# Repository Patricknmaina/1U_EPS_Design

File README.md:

# 1U_EPS_Design
Electrical Power Subsystem design for a 1U CubeSat, following the BIRDS-X Design structure

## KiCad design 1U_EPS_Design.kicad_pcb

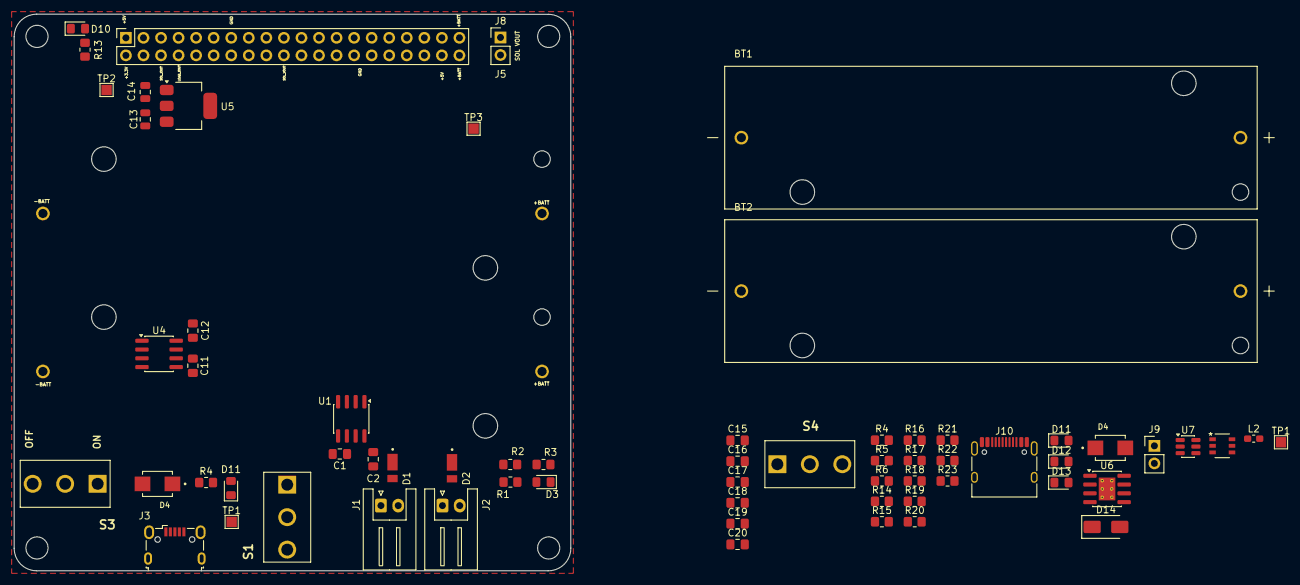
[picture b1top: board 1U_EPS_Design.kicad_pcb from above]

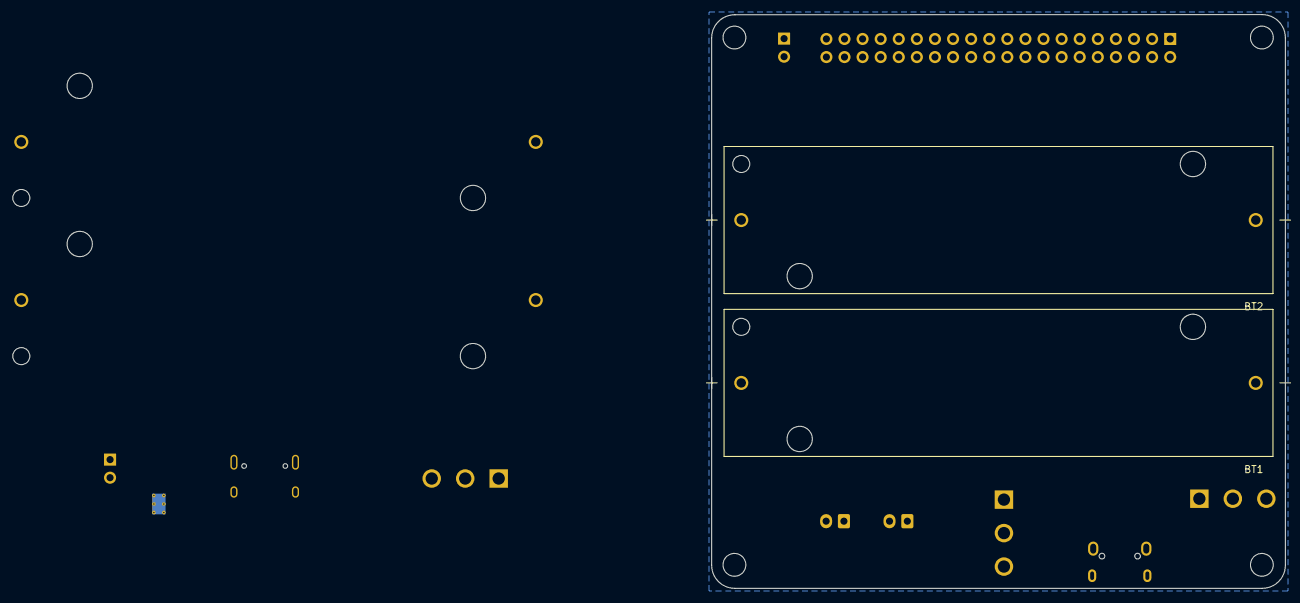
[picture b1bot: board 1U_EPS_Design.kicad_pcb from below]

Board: 2 copper layers, 80.5 x 80.5 mm, 70 parts (2 on the bottom side), 37 nets, no tracks yet.

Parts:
BT1, BT1#2, BT2, BT2#2: 1043; BAT_1043
C1, C11: 1n; C_0805_2012Metric_Pad1.18x1.45mm_HandSolder
C2, C12: 0.1u; C_0805_2012Metric_Pad1.18x1.45mm_HandSolder
C13: 10uF; C_0805_2012Metric
C14: 22uF; C_0805_2012Metric
C15, C16: 10uF; C_0805_2012Metric_Pad1.18x1.45mm_HandSolder
C17: 0.1uF; C_0805_2012Metric_Pad1.18x1.45mm_HandSolder
C18, C19: 22u; C_0805_2012Metric_Pad1.18x1.45mm_HandSolder
C20: 100nF; C_0805_2012Metric_Pad1.18x1.45mm_HandSolder
D1, D2: DFLS130L-7; DIO_DFLS130L-7
D3, D10, D11, D12: LED; LED_0805_2012Metric_Pad1.15x1.40mm_HandSolder
D4, D4#2: SMBJ5.0A; DIOM4336X265N
D11#2: Red LED; LED_0805_2012Metric_Pad1.15x1.40mm_HandSolder
D13: Green LED; LED_0805_2012Metric_Pad1.15x1.40mm_HandSolder
D14: SS34; D_SMA
H1, H2, H3, H4: MountingHole; MountingHole_3.2mm_M3
IC2: DW06D; DW06D_SFE
J1: Solar_Panel_1; JST_XH_S2B-XH-A_1x02_P2.50mm_Horizontal
J2: Solar_Panel_2; JST_XH_S2B-XH-A_1x02_P2.50mm_Horizontal
J3: USB_B_Micro; USB_Micro-B_Wuerth_629105150521
J5: Conn_02x20_Odd_Even; PinSocket_2x20_P2.54mm_Vertical
J8: Conn_01x02_Pin; PinHeader_1x02_P2.54mm_Vertical
J9: Release Detection; PinHeader_1x02_P2.54mm_Vertical
J10: USB_C_Receptacle_USB2.0_16P; USB_C_Receptacle_HRO_TYPE-C-31-M-12
L2: 4.7uH; L_0603_1608Metric_Pad1.05x0.95mm_HandSolder
R1, R4#2, R6, R13, R15, R16, R19, R20: 1k; R_0805_2012Metric_Pad1.20x1.40mm_HandSolder
R2, R18, R22: 10k; R_0805_2012Metric_Pad1.20x1.40mm_HandSolder
R3: 12k; R_0805_2012Metric_Pad1.20x1.40mm_HandSolder
R4: 5.1k; R_0805_2012Metric_Pad1.20x1.40mm_HandSolder
R5: 5,1k; R_0805_2012Metric_Pad1.20x1.40mm_HandSolder
R14: 0.4R; R_0805_2012Metric_Pad1.20x1.40mm_HandSolder
R17: 2.4k; R_0805_2012Metric_Pad1.20x1.40mm_HandSolder
R21: 73.2k; R_0805_2012Metric_Pad1.20x1.40mm_HandSolder
R23: 100k; R_0805_2012Metric_Pad1.20x1.40mm_HandSolder
S1: USB-Solar Toggle; SS12D10L3
S3, S4: Power Switch; SS12D10L3
TP1, TP1#2: TP1_5V; TestPoint_Pad_1.5x1.5mm
TP2: TP2_3.3; TestPoint_Pad_1.5x1.5mm
TP3: TP3_BATT; TestPoint_Pad_1.5x1.5mm
U1, U4: ACS712xLCTR-05B; SOIC-8_3.9x4.9mm_P1.27mm
U5: AMS1117-3.3; SOT-223-3_TabPin2
U6: TP4056-42-ESOP8; SOIC-8-1EP_3.9x4.9mm_P1.27mm_EP2.41x3.3mm_ThermalVias
U7: MT3608; SOT-23-6

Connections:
+3.3V: C14.1, J5.2, TP2.1 (1_1), U5.2 (VO)
+5V: C2.1, C12.1, C13.1, J5.1, J5.38, R13.1, U1.8 (VCC), U4.3 (IP-), U4.4 (IP-), U4.8 (VCC), U5.3 (VI)
+BATT: BT1.P, BT1#2.P, BT2.P, BT2#2.P, C16.1, C18.1, J5.39, J5.40, L2.1, R19.1, R23.1, TP3.1 (1_1), U6.5 (BAT), U7.5 (IN)
/LOAD_IOUT: J5.8, U4.7 (VIOUT)
/SOL_IOUT: J5.6, U1.7 (VIOUT)
/SOL_VOUT: J5.20, J8.1
/VIN: R14.1, S1.2 (COM)
/VOUT: C19.1, D14.1 (K), R21.1, U4.1 (IP+), U4.2 (IP+)
GND: C1.2, C2.2, C11.2, C12.2, C13.2, C14.2, C15.2, C16.2, C18.2, C19.2, C20.2, D3.1 (K), D4.A, D4#2.A, D10.1 (K), D11.1 (K), D12.1 (K), IC2.2 (S1), J1.2, J2.2, J3.5 (GND), J3.6 (Shield), J5.13, J5.28, J9.1, J10.A1 (GND), J10.A12 (GND), J10.B1 (GND), J10.B12 (GND), J10.SH (SHIELD), R3.2, R4.2, R5.2, R17.2, R18.2, R20.2, R22.2, S4.1 (NC), U1.5 (GND), U4.5 (GND), U5.1 (GND), U6.3 (GND), U6.9 (EPAD), U7.2 (GND)
unnamed: D1.C, D2.C, R1.1, R2.1, U1.1 (IP+), U1.2 (IP+)
unnamed: D3.2 (A), R1.2
unnamed: D10.2 (A), R13.2
unnamed: D11.2 (A), D11#2.2 (A), R4#2.2, U6.7 (~CHRG)
unnamed: D11#2.1 (K), R16.2
unnamed: D12.2 (A), R6.2
unnamed: D13.2 (A), U6.6 (~STDBY)
unnamed: D13.1 (K), R15.2
unnamed: D14.2 (A), L2.2, U7.1 (SW)
unnamed: BT1.N, BT2.N, C17.1, IC2.3 (S2), IC2.6 (VSS)
unnamed: IC2.1 (V-), R20.1
unnamed: C17.2, IC2.5 (VDD), R19.2
unnamed: D1.A, J1.1
unnamed: D2.A, J2.1
unnamed: D4#2.C, J3.1 (VBUS), R4#2.1, TP1.1
unnamed: BT1#2.N, BT2#2.N
unnamed: J8.2, R2.2, R3.1
unnamed: C20.1, J9.2, R23.2, S4.2 (COM), U7.4 (EN)
unnamed: J10.A5 (CC1), R5.1
unnamed: J10.B5 (CC2), R4.1
unnamed: S1.1 (NC), U1.3 (IP-), U1.4 (IP-)
unnamed: D4.C, J10.A4 (VBUS), J10.A9 (VBUS), J10.B4 (VBUS), J10.B9 (VBUS), R6.1, S1.3 (NO), TP1#2.1 (1_1)
unnamed: C1.1, U1.6 (FILTER)
unnamed: C11.1, U4.6 (FILTER)
unnamed: C15.1, R14.2, R15.1, R16.1, U6.4 (V_{CC}), U6.8 (CE)
unnamed: R17.1, U6.2 (PROG)
unnamed: R18.1, U6.1 (TEMP)
unnamed: R21.2, R22.1, U7.3 (FB)
